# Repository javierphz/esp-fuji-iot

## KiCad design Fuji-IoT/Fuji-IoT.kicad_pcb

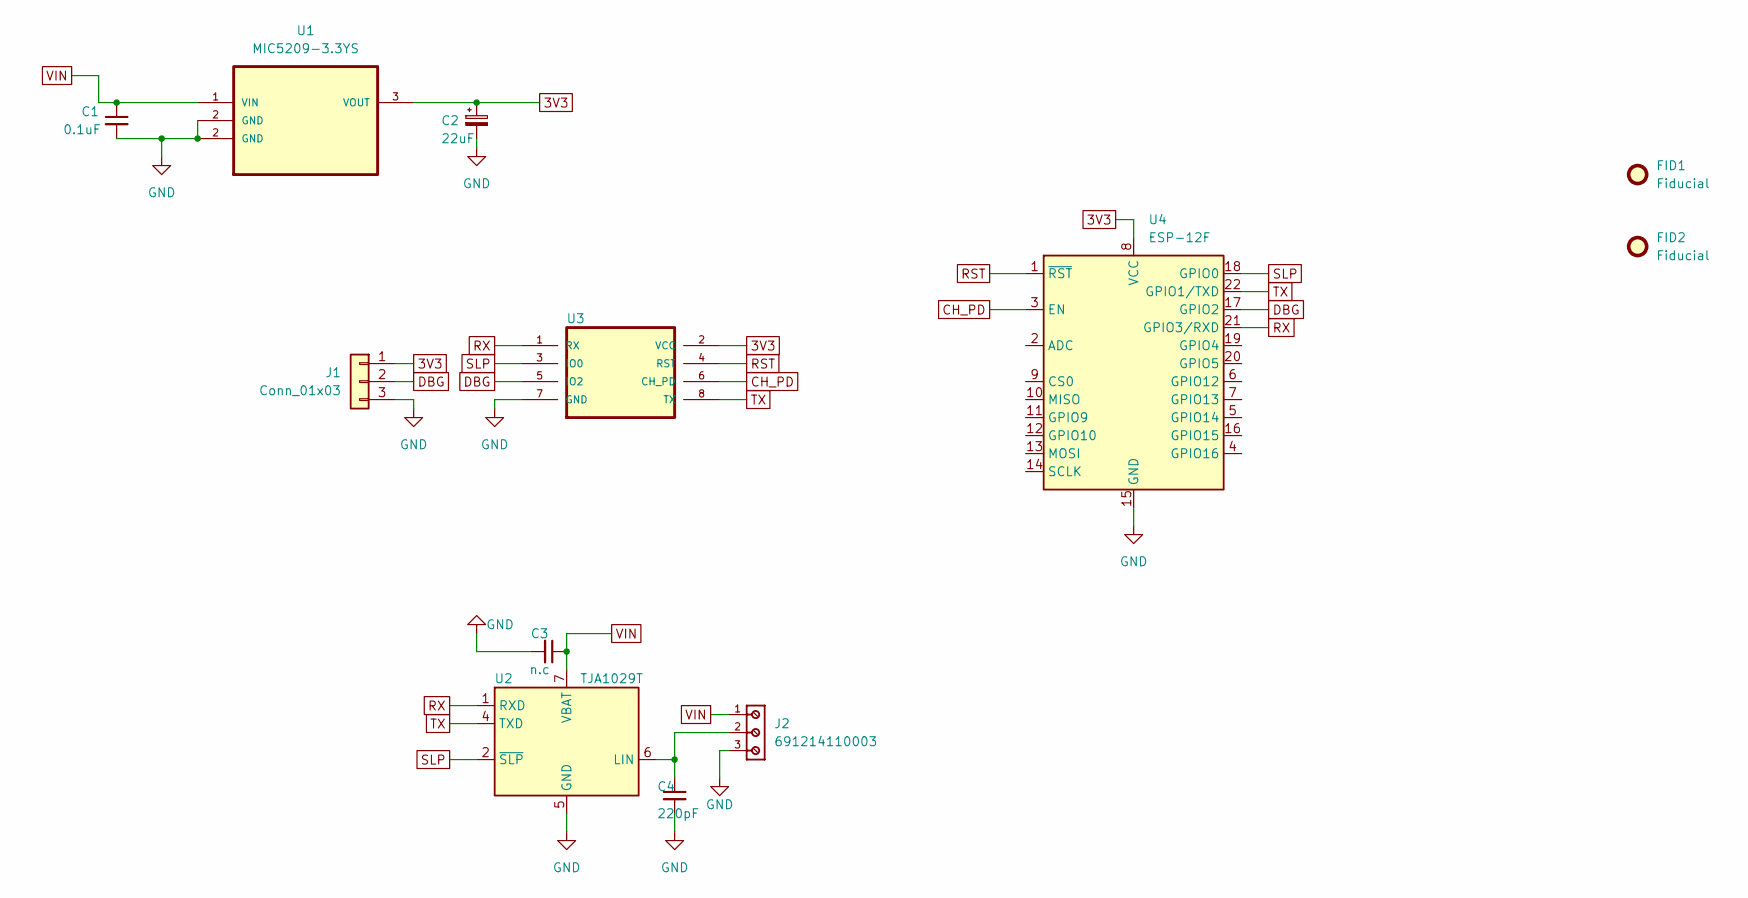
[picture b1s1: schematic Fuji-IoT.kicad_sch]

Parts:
C1: 0.1uF; C_0603_1608Metric_Pad1.08x0.95mm_HandSolder
C2: 22uF; CP_EIA-7361-438_AVX-U_Pad2.18x3.30mm_HandSolder
C3: n.c; C_0805_2012Metric_Pad1.18x1.45mm_HandSolder
C4: 220pF; C_0805_2012Metric_Pad1.18x1.45mm_HandSolder
FID1, FID2: Fiducial; Fiducial_0.5mm_Mask1.5mm
J1: Conn_01x03; PinHeader_1x03_P2.54mm_Vertical
J2: 691214110003; PART-NUMBER 691214110003
U1: MIC5209-3.3YS; SOT-223-3_TabPin2
U2: TJA1029T; SOIC-8_3.9x4.9mm_P1.27mm
U3: ESP-01
U4: ESP-12F; ESP-12E

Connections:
3V3: C2.1, J1.1, U1.3 (VOUT), U3.2 (VCC), U4.8 (VCC)
CH_PD: U3.6 (CH_PD), U4.3 (EN)
DBG: J1.2, U3.5 (IO2), U4.17 (GPIO2)
GND: C1.2, C2.2, C3.2, C4.2, J1.3, J2.3, U1.2 (GND), U2.5 (GND), U3.7 (GND), U4.15 (GND)
unnamed: C4.1, J2.2, U2.6 (LIN)
RST: U3.4 (RST), U4.1 (~RST)
RX: U2.1 (RXD), U3.1 (RX), U4.21 (GPIO3/RXD)
SLP: U2.2 (~SLP), U3.3 (IO0), U4.18 (GPIO0)
TX: U2.4 (TXD), U3.8 (TX), U4.22 (GPIO1/TXD)
VIN: C1.1, C3.1, J2.1, U1.1 (VIN), U2.7 (VBAT)

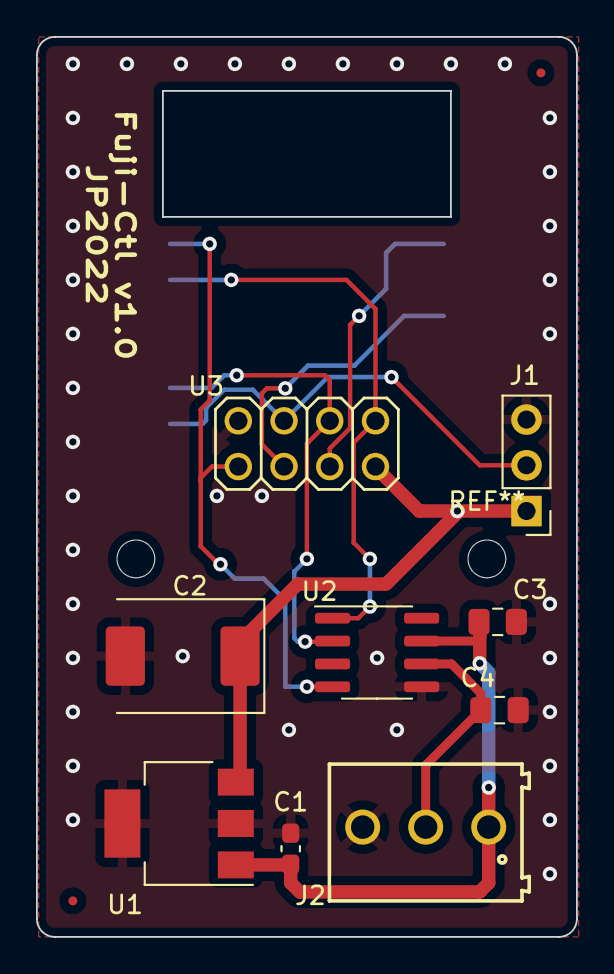
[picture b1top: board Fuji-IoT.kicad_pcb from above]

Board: 2 copper layers, 30.0 x 50.0 mm, 12 parts (1 on the bottom side), 10 nets.
